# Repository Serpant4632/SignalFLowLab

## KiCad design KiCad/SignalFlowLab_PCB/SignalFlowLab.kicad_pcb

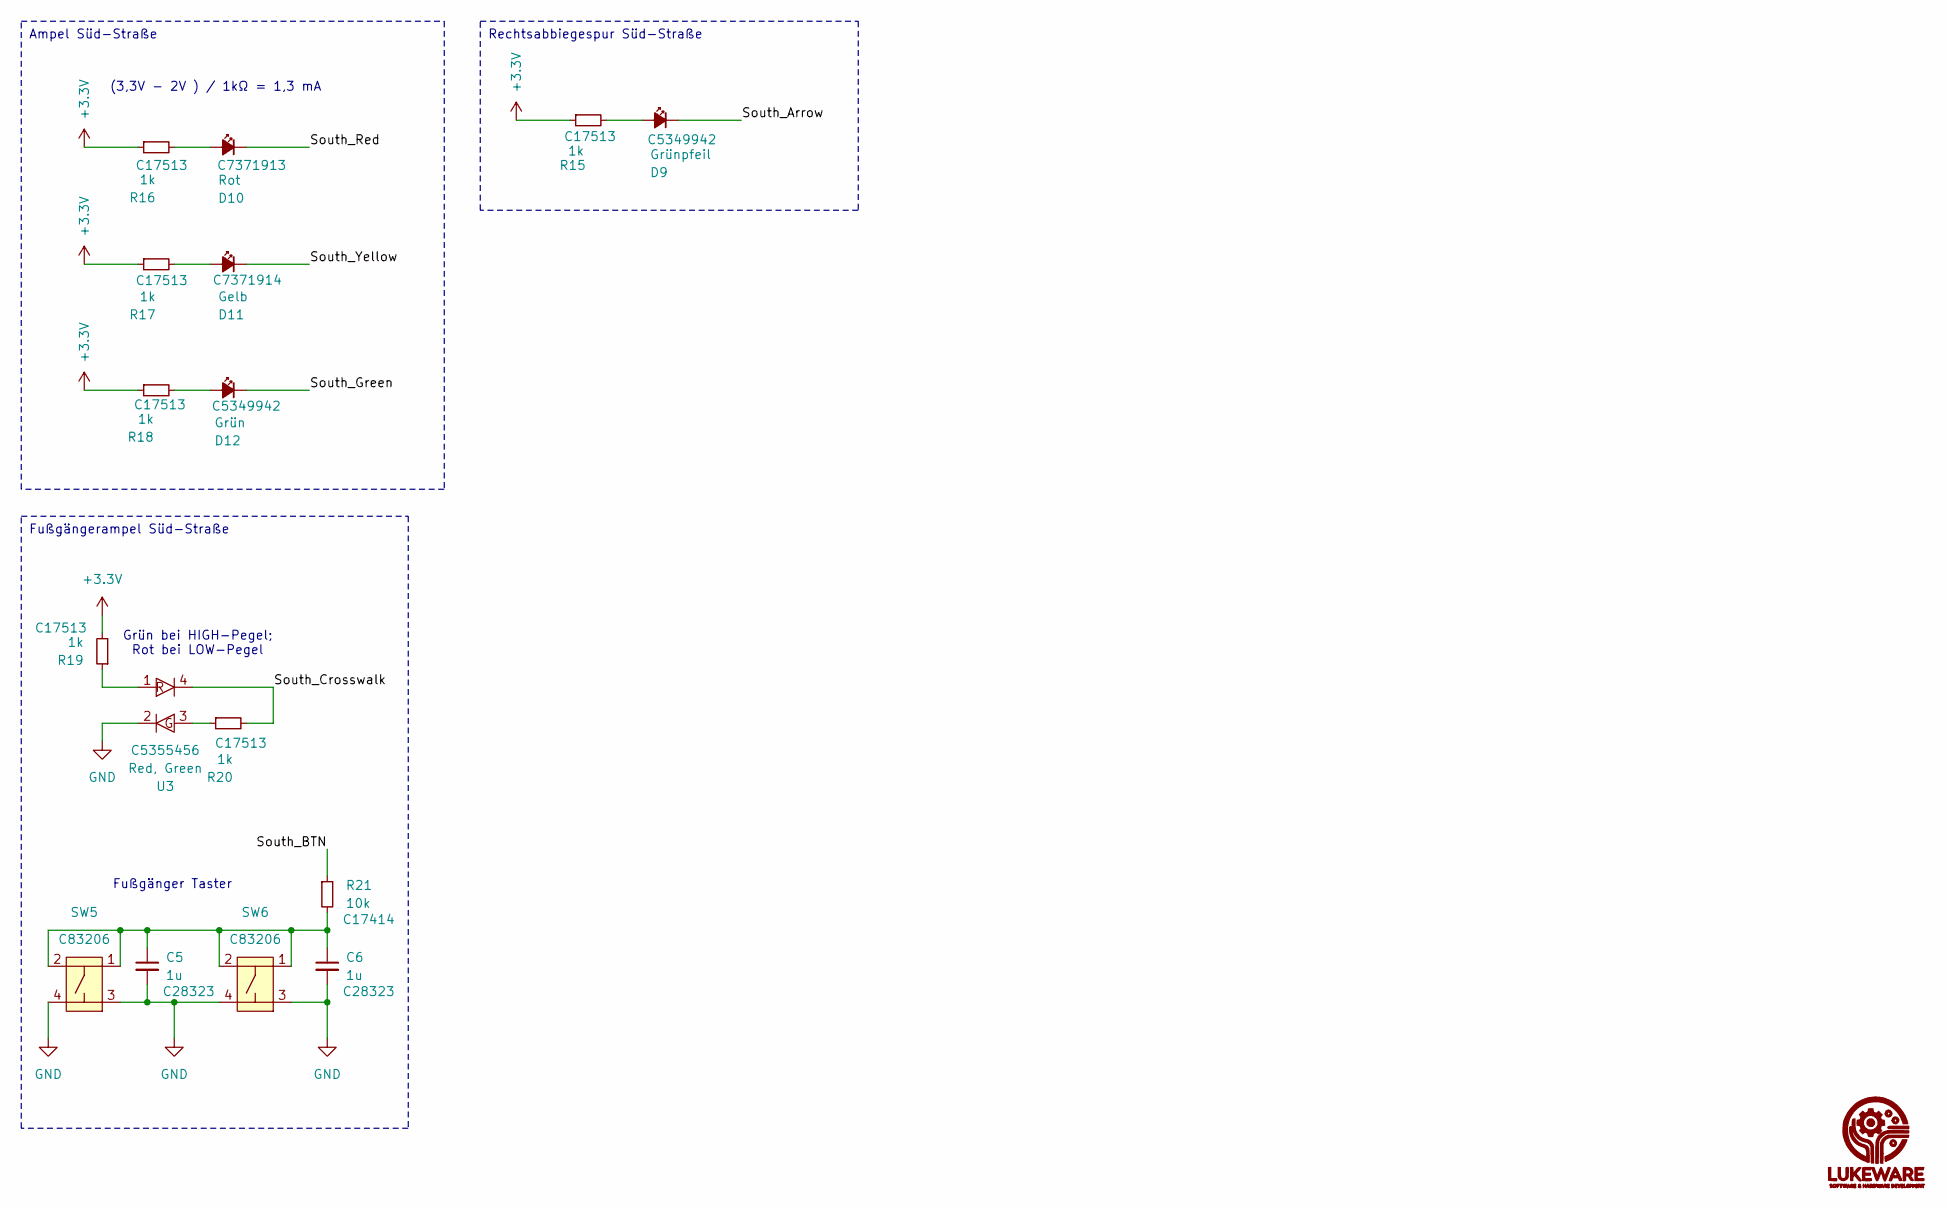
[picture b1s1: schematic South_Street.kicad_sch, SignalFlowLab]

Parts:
C5, C6: 1u; C_0805_2012Metric; LCSC C28323
D9: Grünpfeil; LED_0805_2012Metric; LCSC C5349942
D10: Rot; LED_0805_2012Metric; LCSC C7371913
D11: Gelb; LED_0805_2012Metric; LCSC C7371914
D12: Grün; LED_0805_2012Metric; LCSC C5349942
R15, R16, R17, R18, R19, R20: 1k; R_0805_2012Metric; LCSC C17513
R21: 10k; R_0805_2012Metric; LCSC C17414
SW5, SW6: K2-6639SP-C4SC-04; LCSC C83206
U3: Red, Green; A-SC6302R6AGHC-A03-2T; LCSC C5355456

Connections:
+3.3V: R15.1, R16.1, R17.1, R18.1, R19.2; also elsewhere on the board
/South_Street/South_Arrow: D9.1 (K)
/South_Street/South_BTN: R21.1
/South_Street/South_Crosswalk: R20.2, U3.4
/South_Street/South_Green: D12.1 (K)
/South_Street/South_Red: D10.1 (K)
/South_Street/South_Yellow: D11.1 (K)
GND: C5.2, C6.2, SW5.3, SW5.4, SW6.3, SW6.4, U3.2; also elsewhere on the board
unnamed: C5.1, C6.1, R21.2, SW5.1, SW5.2, SW6.1, SW6.2
unnamed: D9.2 (A), R15.2
unnamed: D10.2 (A), R16.2
unnamed: D11.2 (A), R17.2
unnamed: D12.2 (A), R18.2
unnamed: R19.1, U3.1
unnamed: R20.1, U3.3

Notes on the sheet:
Fußgängerampel Süd-Straße
Rechtsabbiegespur Süd-Straße
Ampel Süd-Straße
Grün bei HIGH-Pegel; Rot bei LOW-Pegel
Fußgänger Taster
(3,3V - 2V ) / 1kΩ = 1,3 mA

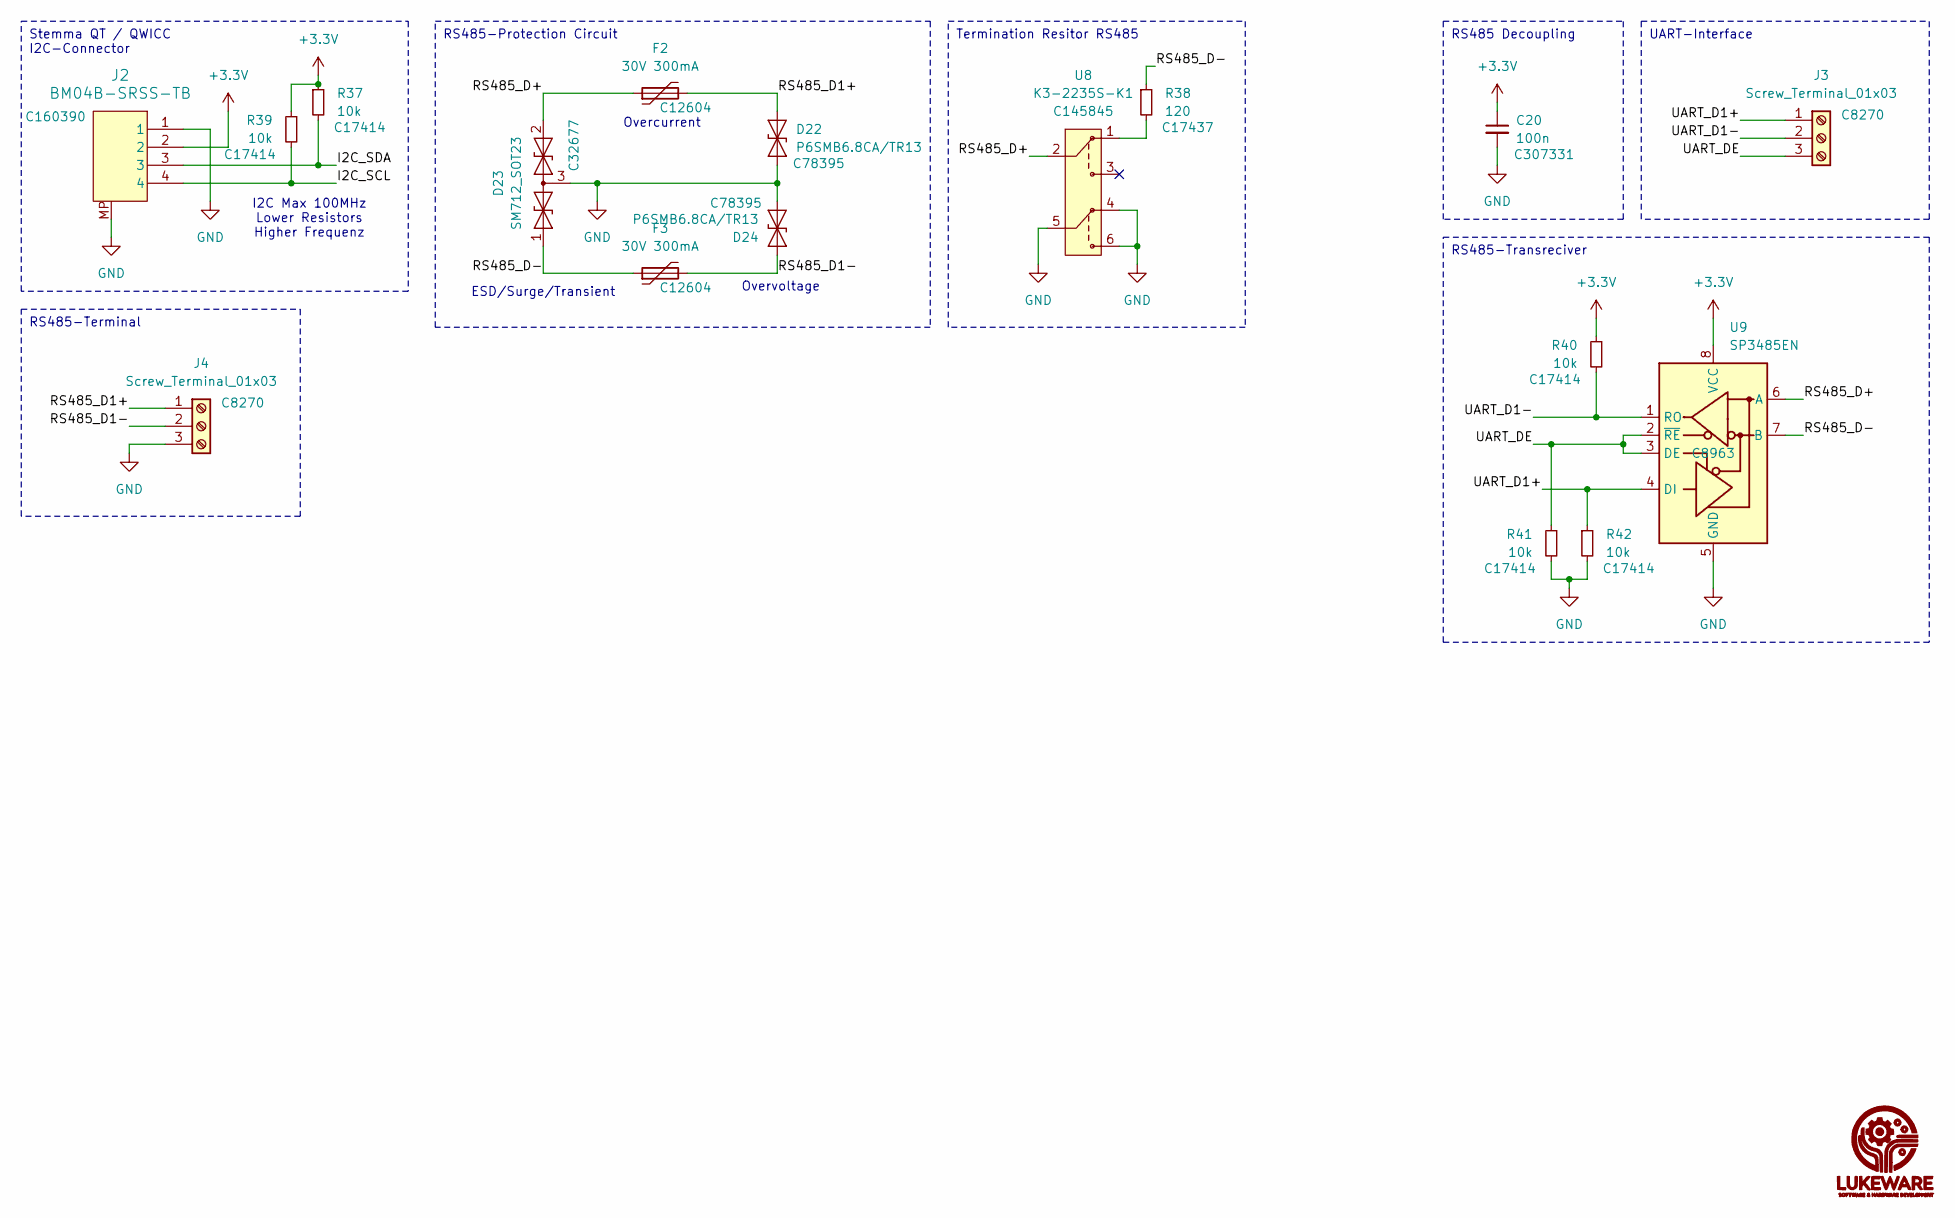
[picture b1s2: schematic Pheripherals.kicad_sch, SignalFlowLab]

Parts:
C20: 100n; C_0402_1005Metric; LCSC C307331
D22, D24: P6SMB6.8CA/TR13; D_SMB; LCSC C78395
D23: SM712_SOT23; SOT-23; LCSC C32677
F2, F3: 30V 300mA; Fuse_1812_4532Metric; LCSC C12604
J2: BM04B-SRSS-TB; CONN4_BM04B-SRSS_JST; LCSC C160390
J3, J4: Screw_Terminal_01x03; TerminalBlock_Phoenix_PT-1,5-3-5.0-H_1x03_P5.00mm_Horizontal; LCSC C8270
R37, R39, R40, R41, R42: 10k; R_0805_2012Metric; LCSC C17414
R38: 120; R_0805_2012Metric; LCSC C17437
U8: K3-2235S-K1; LCSC C145845
U9: SP3485EN; SOIC-8_3.9x4.9mm_P1.27mm; LCSC C8963

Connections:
+3.3V: C20.1, J2.2, R37.1, R39.1, R40.1, U9.8 (VCC); also elsewhere on the board
/Pheripherals/I2C_SCL: J2.4, R39.2
/Pheripherals/I2C_SDA: J2.3, R37.2
/Pheripherals/RS485_D1+: D22.2 (A2), F2.2, J4.1
/Pheripherals/RS485_D1-: D24.2 (A2), F3.2, J4.2
/Pheripherals/RS485_D+: D23.2 (A2), F2.1, U8.2, U9.6 (A)
/Pheripherals/RS485_D-: D23.1 (A1), F3.1, R38.1, U9.7 (B)
/Pheripherals/UART_D1+: J3.1, R42.1, U9.4 (DI)
/Pheripherals/UART_D1-: J3.2, R40.2, U9.1 (RO)
/Pheripherals/UART_DE: J3.3, R41.1, U9.2 (~RE), U9.3 (DE)
GND: C20.2, D22.1 (A1), D23.3 (common), D24.1 (A1), J2.1, J2.MP, J4.3, R41.2, R42.2, U8.4, U8.5, U8.6, U9.5 (GND); also elsewhere on the board
unnamed: R38.2, U8.1

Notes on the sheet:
Termination Resitor RS485
Stemma QT / QWICC I2C-Connector
RS485 Decoupling
RS485-Transreciver
RS485-Terminal
RS485-Protection Circuit
UART-Interface
ESD/Surge/Transient
Overvoltage
I2C Max 100MHz Lower Resistors Higher Frequenz
Overcurrent

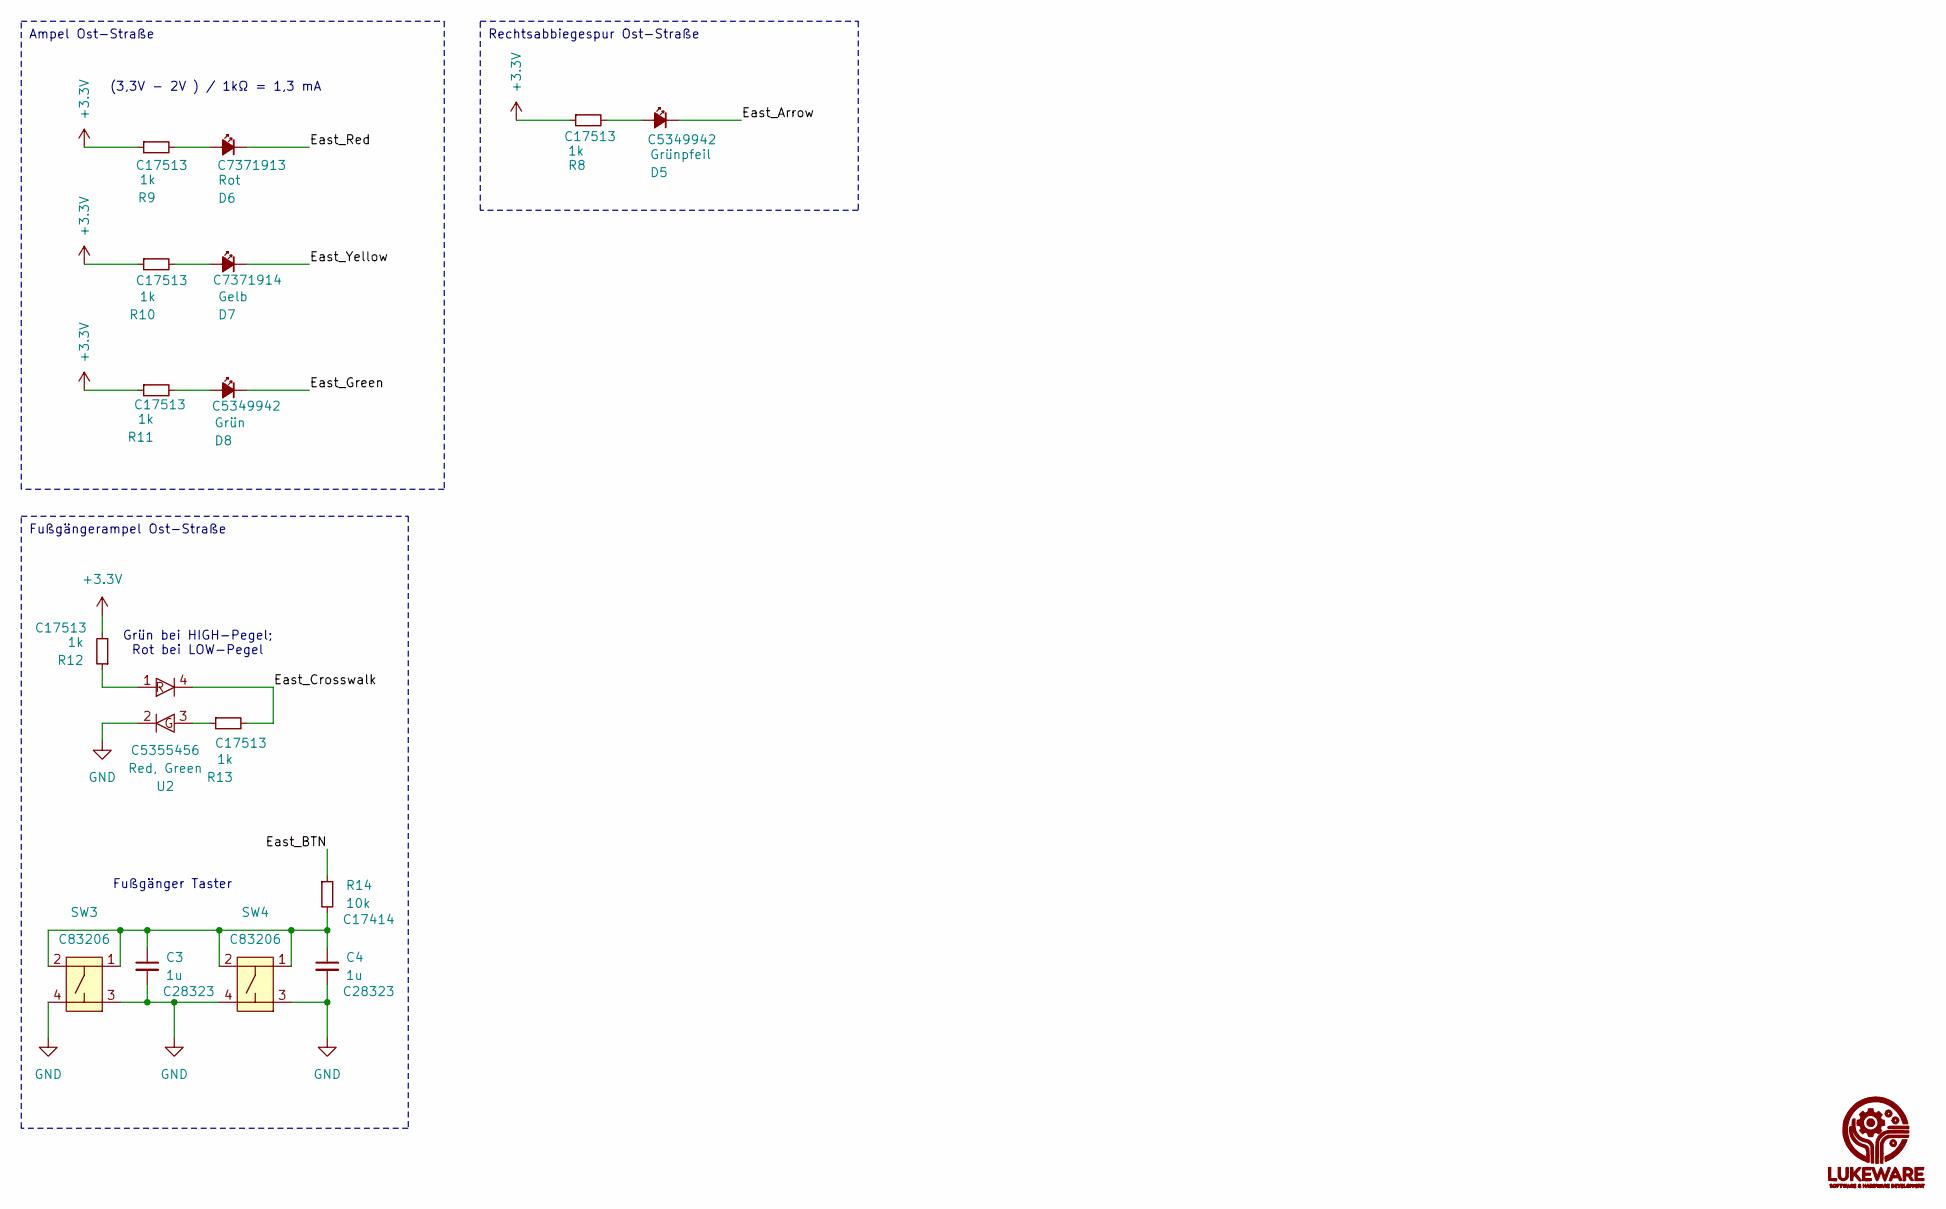
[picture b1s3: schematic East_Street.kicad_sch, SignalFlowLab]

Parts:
C3, C4: 1u; C_0805_2012Metric; LCSC C28323
D5: Grünpfeil; LED_0805_2012Metric; LCSC C5349942
D6: Rot; LED_0805_2012Metric; LCSC C7371913
D7: Gelb; LED_0805_2012Metric; LCSC C7371914
D8: Grün; LED_0805_2012Metric; LCSC C5349942
R8, R9, R10, R11, R12, R13: 1k; R_0805_2012Metric; LCSC C17513
R14: 10k; R_0805_2012Metric; LCSC C17414
SW3, SW4: K2-6639SP-C4SC-04; LCSC C83206
U2: Red, Green; A-SC6302R6AGHC-A03-2T; LCSC C5355456

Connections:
+3.3V: R8.1, R9.1, R10.1, R11.1, R12.2; also elsewhere on the board
/East_Street/East_Arrow: D5.1 (K)
/East_Street/East_BTN: R14.1
/East_Street/East_Crosswalk: R13.2, U2.4
/East_Street/East_Green: D8.1 (K)
/East_Street/East_Red: D6.1 (K)
/East_Street/East_Yellow: D7.1 (K)
GND: C3.2, C4.2, SW3.3, SW3.4, SW4.3, SW4.4, U2.2; also elsewhere on the board
unnamed: C3.1, C4.1, R14.2, SW3.1, SW3.2, SW4.1, SW4.2
unnamed: D5.2 (A), R8.2
unnamed: D6.2 (A), R9.2
unnamed: D7.2 (A), R10.2
unnamed: D8.2 (A), R11.2
unnamed: R12.1, U2.1
unnamed: R13.1, U2.3

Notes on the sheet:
Fußgängerampel Ost-Straße
Rechtsabbiegespur Ost-Straße
Ampel Ost-Straße
Grün bei HIGH-Pegel; Rot bei LOW-Pegel
Fußgänger Taster
(3,3V - 2V ) / 1kΩ = 1,3 mA

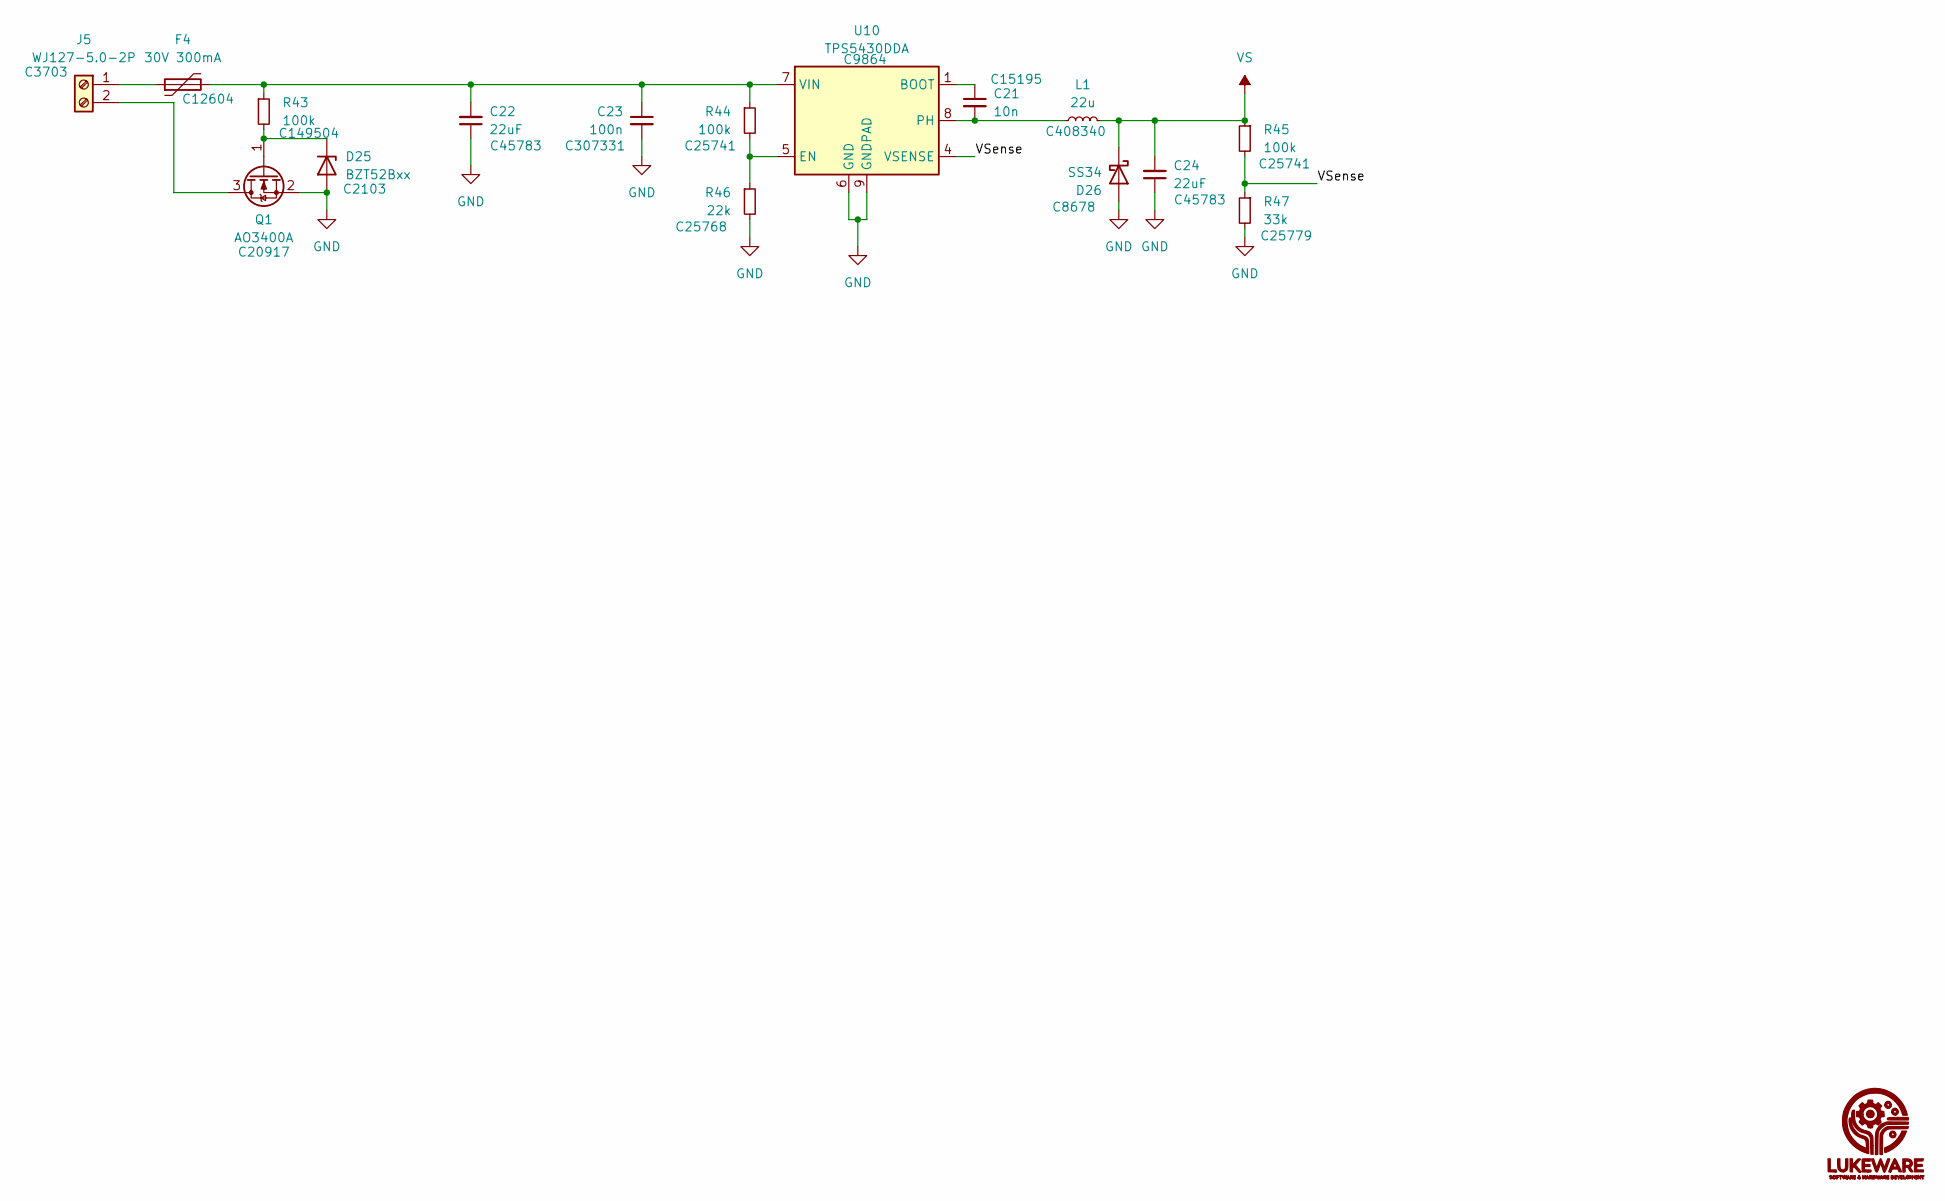
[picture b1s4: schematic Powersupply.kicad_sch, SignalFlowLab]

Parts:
C21: 10n; C_0402_1005Metric; LCSC C15195
C22, C24: 22uF; C_0805_2012Metric; LCSC C45783
C23: 100n; C_0402_1005Metric; LCSC C307331
D25: BZT52Bxx; D_SOD-123; LCSC C2103
D26: SS34; D_SMA; LCSC C8678
F4: 30V 300mA; Fuse_1812_4532Metric; LCSC C12604
J5: WJ127-5.0-2P; TerminalBlock_Phoenix_PT-1,5-2-5.0-H_1x02_P5.00mm_Horizontal; LCSC C3703
L1: 22u; L_Sunlord_MWSA0402S; LCSC C408340
Q1: AO3400A; SOT-23; LCSC C20917
R43: 100k; C_0805_2012Metric; LCSC C149504
R44, R45: 100k; R_0402_1005Metric; LCSC C25741
R46: 22k; R_0402_1005Metric; LCSC C25768
R47: 33k; R_0402_1005Metric; LCSC C25779
U10: TPS5430DDA; TI_SO-PowerPAD-8_ThermalVias; LCSC C9864

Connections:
/Powersupply/VSense: R45.2, R47.1, U10.4 (VSENSE)
GND: C22.1, C23.2, C24.1, D25.2 (A), D26.2 (A), Q1.2 (S), R46.2, R47.2, U10.6 (GND), U10.9 (GNDPAD); also elsewhere on the board
unnamed: D25.1 (K), Q1.1 (G), R43.2
unnamed: F4.1, J5.1
unnamed: J5.2, Q1.3 (D)
unnamed: C21.1, U10.1 (BOOT)
unnamed: R44.2, R46.1, U10.5 (EN)
unnamed: C21.2, L1.2, U10.8 (PH)
unnamed: C22.2, C23.1, F4.2, R43.1, R44.1, U10.7 (VIN)
VS: C24.2, D26.1 (K), L1.1, R45.1; also elsewhere on the board

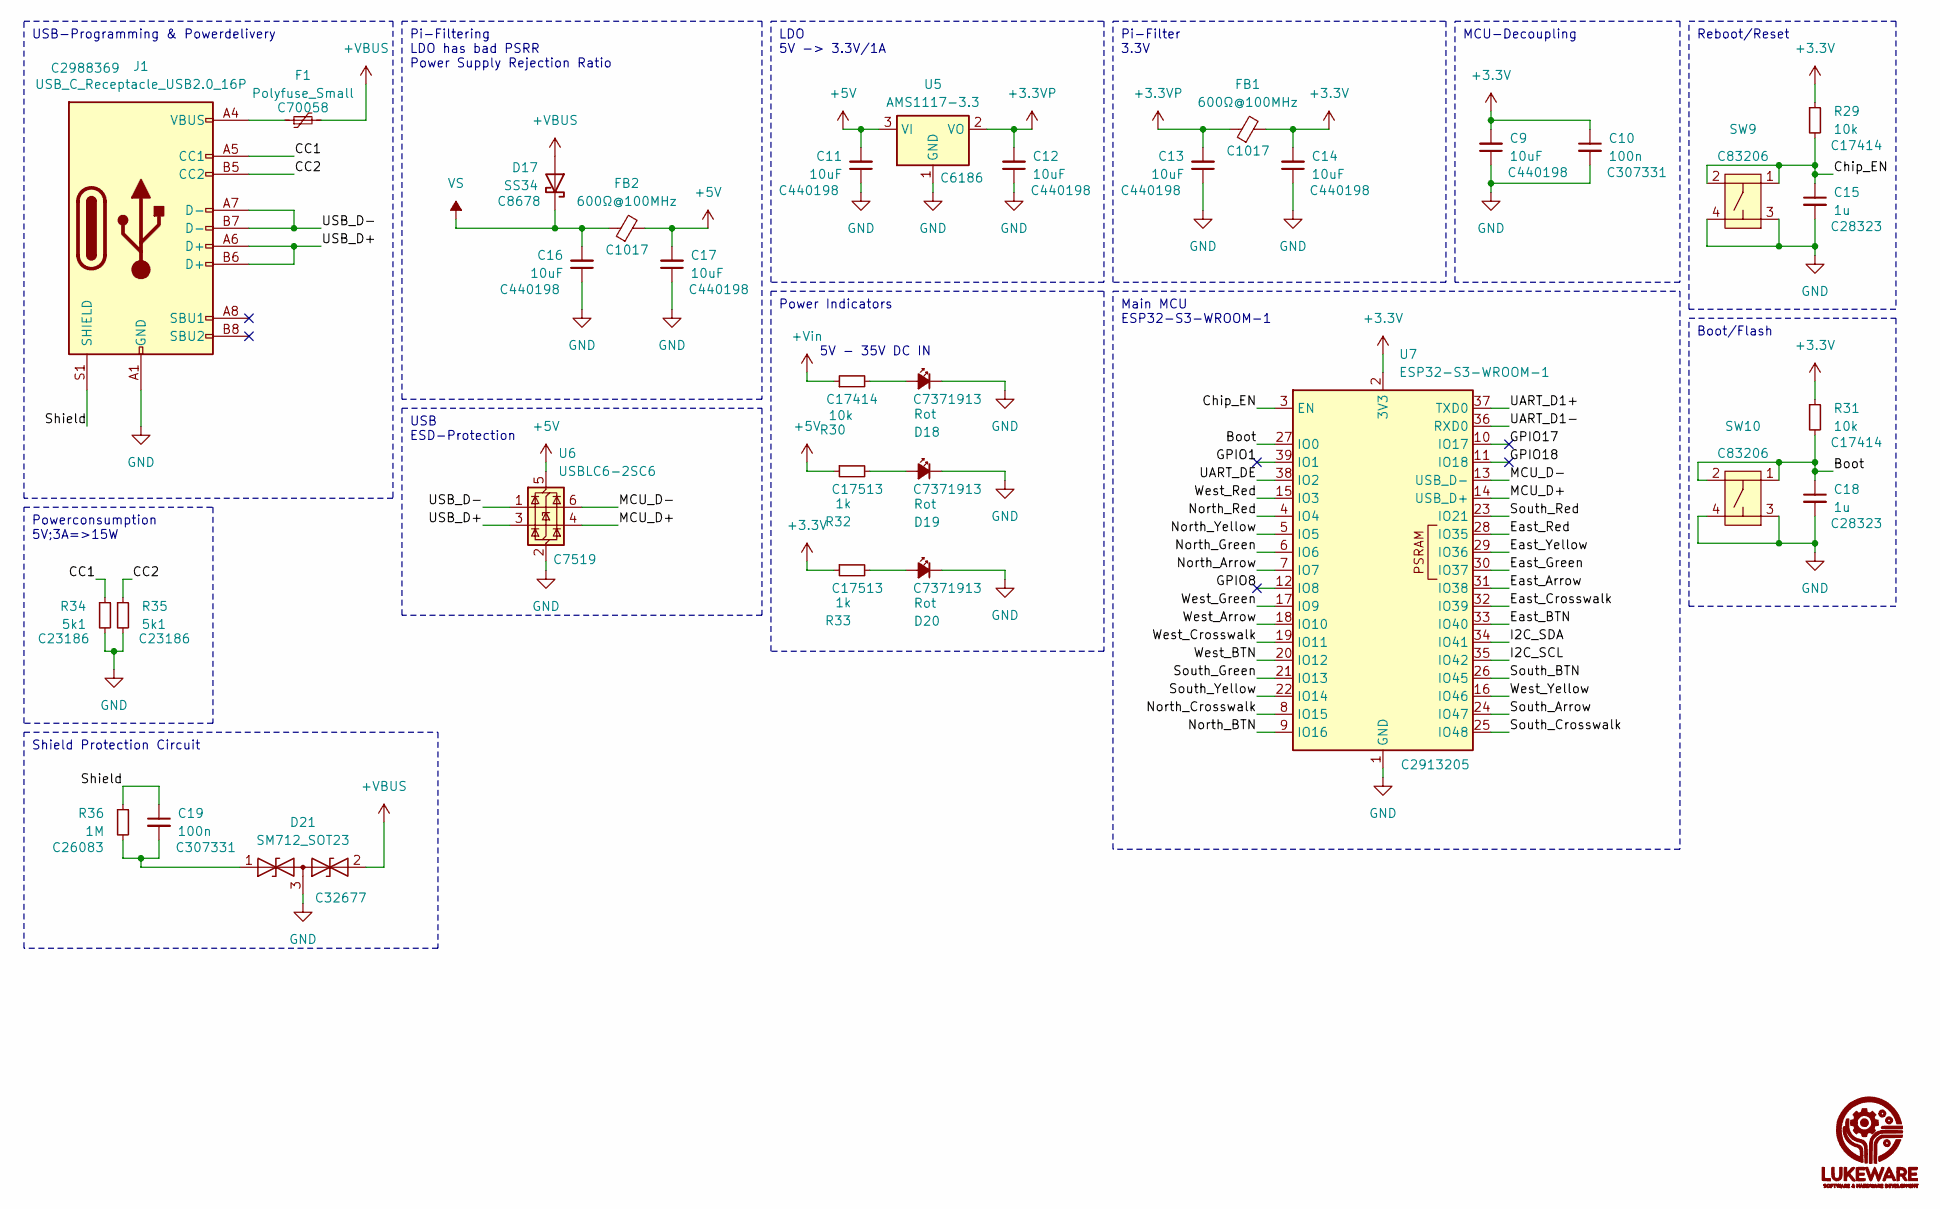
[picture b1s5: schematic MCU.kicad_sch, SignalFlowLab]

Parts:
C9, C11, C12, C13, C14, C16, C17: 10uF; C_0805_2012Metric; LCSC C440198
C10, C19: 100n; C_0402_1005Metric; LCSC C307331
C15, C18: 1u; C_0805_2012Metric; LCSC C28323
D17: SS34; D_SMA; LCSC C8678
D18, D19, D20: Rot; LED_0805_2012Metric; LCSC C7371913
D21: SM712_SOT23; SOT-23; LCSC C32677
F1: Polyfuse_Small; Fuse_0805_2012Metric; LCSC C70058
FB1, FB2: 600Ω@100MHz; L_0805_2012Metric; LCSC C1017
J1: USB_C_Receptacle_USB2.0_16P; USB_C_Receptacle_G-Switch_GT-USB-7010ASV; LCSC C2988369
R29, R30, R31: 10k; R_0805_2012Metric; LCSC C17414
R32, R33: 1k; R_0805_2012Metric; LCSC C17513
R34, R35: 5k1; R_0603_1608Metric; LCSC C23186
R36: 1M; R_0402_1005Metric; LCSC C26083
SW9, SW10: K2-6639SP-C4SC-04; LCSC C83206
U5: AMS1117-3.3; SOT-223-3_TabPin2; LCSC C6186
U6: USBLC6-2SC6; SOT-23-6; LCSC C7519
U7: ESP32-S3-WROOM-1; LCSC C2913205

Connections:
+3.3V: C9.2, C10.1, C14.2, FB1.2, R29.1, R31.1, R33.1, U7.2 (3V3); also elsewhere on the board
+3.3VP: C12.2, C13.2, FB1.1, U5.2 (VO)
+5V: C11.2, C17.2, FB2.2, R32.1, U5.3 (VI), U6.5 (VBUS)
+VBUS: D17.2 (A), D21.2 (A2), F1.2
+Vin: R30.1
/MCU/Boot: C18.1, R31.2, SW10.1, SW10.2, U7.27 (IO0)
/MCU/CC1: J1.A5 (CC1), R34.1
/MCU/CC2: J1.B5 (CC2), R35.1
/MCU/Chip_EN: C15.1, R29.2, SW9.1, SW9.2, U7.3 (EN)
/MCU/East_Arrow: U7.31 (IO38)
/MCU/East_BTN: U7.33 (IO40)
/MCU/East_Crosswalk: U7.32 (IO39)
/MCU/East_Green: U7.30 (IO37)
/MCU/East_Red: U7.28 (IO35)
/MCU/East_Yellow: U7.29 (IO36)
/MCU/GPIO1: U7.39 (IO1)
/MCU/GPIO8: U7.12 (IO8)
/MCU/GPIO17: U7.10 (IO17)
/MCU/GPIO18: U7.11 (IO18)
/MCU/I2C_SCL: U7.35 (IO42)
/MCU/I2C_SDA: U7.34 (IO41)
/MCU/MCU_D+: U6.4 (I/O2), U7.14 (USB_D+)
/MCU/MCU_D-: U6.6 (I/O1), U7.13 (USB_D-)
/MCU/North_Arrow: U7.7 (IO7)
/MCU/North_BTN: U7.9 (IO16)
/MCU/North_Crosswalk: U7.8 (IO15)
/MCU/North_Green: U7.6 (IO6)
/MCU/North_Red: U7.4 (IO4)
/MCU/North_Yellow: U7.5 (IO5)
/MCU/Shield: C19.1, J1.S1 (SHIELD), R36.1
/MCU/South_Arrow: U7.24 (IO47)
/MCU/South_BTN: U7.26 (IO45)
/MCU/South_Crosswalk: U7.25 (IO48)
/MCU/South_Green: U7.21 (IO13)
/MCU/South_Red: U7.23 (IO21)
/MCU/South_Yellow: U7.22 (IO14)
/MCU/UART_D1+: U7.37 (TXD0)
/MCU/UART_D1-: U7.36 (RXD0)
/MCU/UART_DE: U7.38 (IO2)
/MCU/USB_D+: J1.A6 (D+), J1.B6 (D+), U6.3 (I/O2)
/MCU/USB_D-: J1.A7 (D-), J1.B7 (D-), U6.1 (I/O1)
/MCU/West_Arrow: U7.18 (IO10)
/MCU/West_BTN: U7.20 (IO12)
/MCU/West_Crosswalk: U7.19 (IO11)
/MCU/West_Green: U7.17 (IO9)
/MCU/West_Red: U7.15 (IO3)
/MCU/West_Yellow: U7.16 (IO46)
GND: C9.1, C10.2, C11.1, C12.1, C13.1, C14.1, C15.2, C16.1, C17.1, C18.2, D18.1 (K), D19.1 (K), D20.1 (K), D21.3 (common), J1.A1 (GND), J1.A12 (GND), J1.B1 (GND), J1.B12 (GND), R34.2, R35.2, SW9.3, SW9.4, SW10.3, SW10.4, U5.1 (GND), U6.2 (GND), U7.1 (GND), U7.40 (GND), U7.41 (GND); also elsewhere on the board
unnamed: D18.2 (A), R30.2
unnamed: D19.2 (A), R32.2
unnamed: D20.2 (A), R33.2
unnamed: C19.2, D21.1 (A1), R36.2
unnamed: F1.1, J1.A4 (VBUS), J1.A9 (VBUS), J1.B4 (VBUS), J1.B9 (VBUS)
VS: C16.2, D17.1 (K), FB2.1; also elsewhere on the board

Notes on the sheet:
Pi-Filter 3.3V
Reboot/Reset
Power Indicators
USB-Programming & Powerdelivery
Shield Protection Circuit
MCU-Decoupling
USB ESD-Protection
LDO 5V -> 3.3V/1A
Pi-Filtering LDO has bad PSRR Power Supply Rejection Ratio
Main MCU ESP32-S3-WROOM-1
Powerconsumption 5V;3A=>15W
Boot/Flash
5V - 35V DC IN

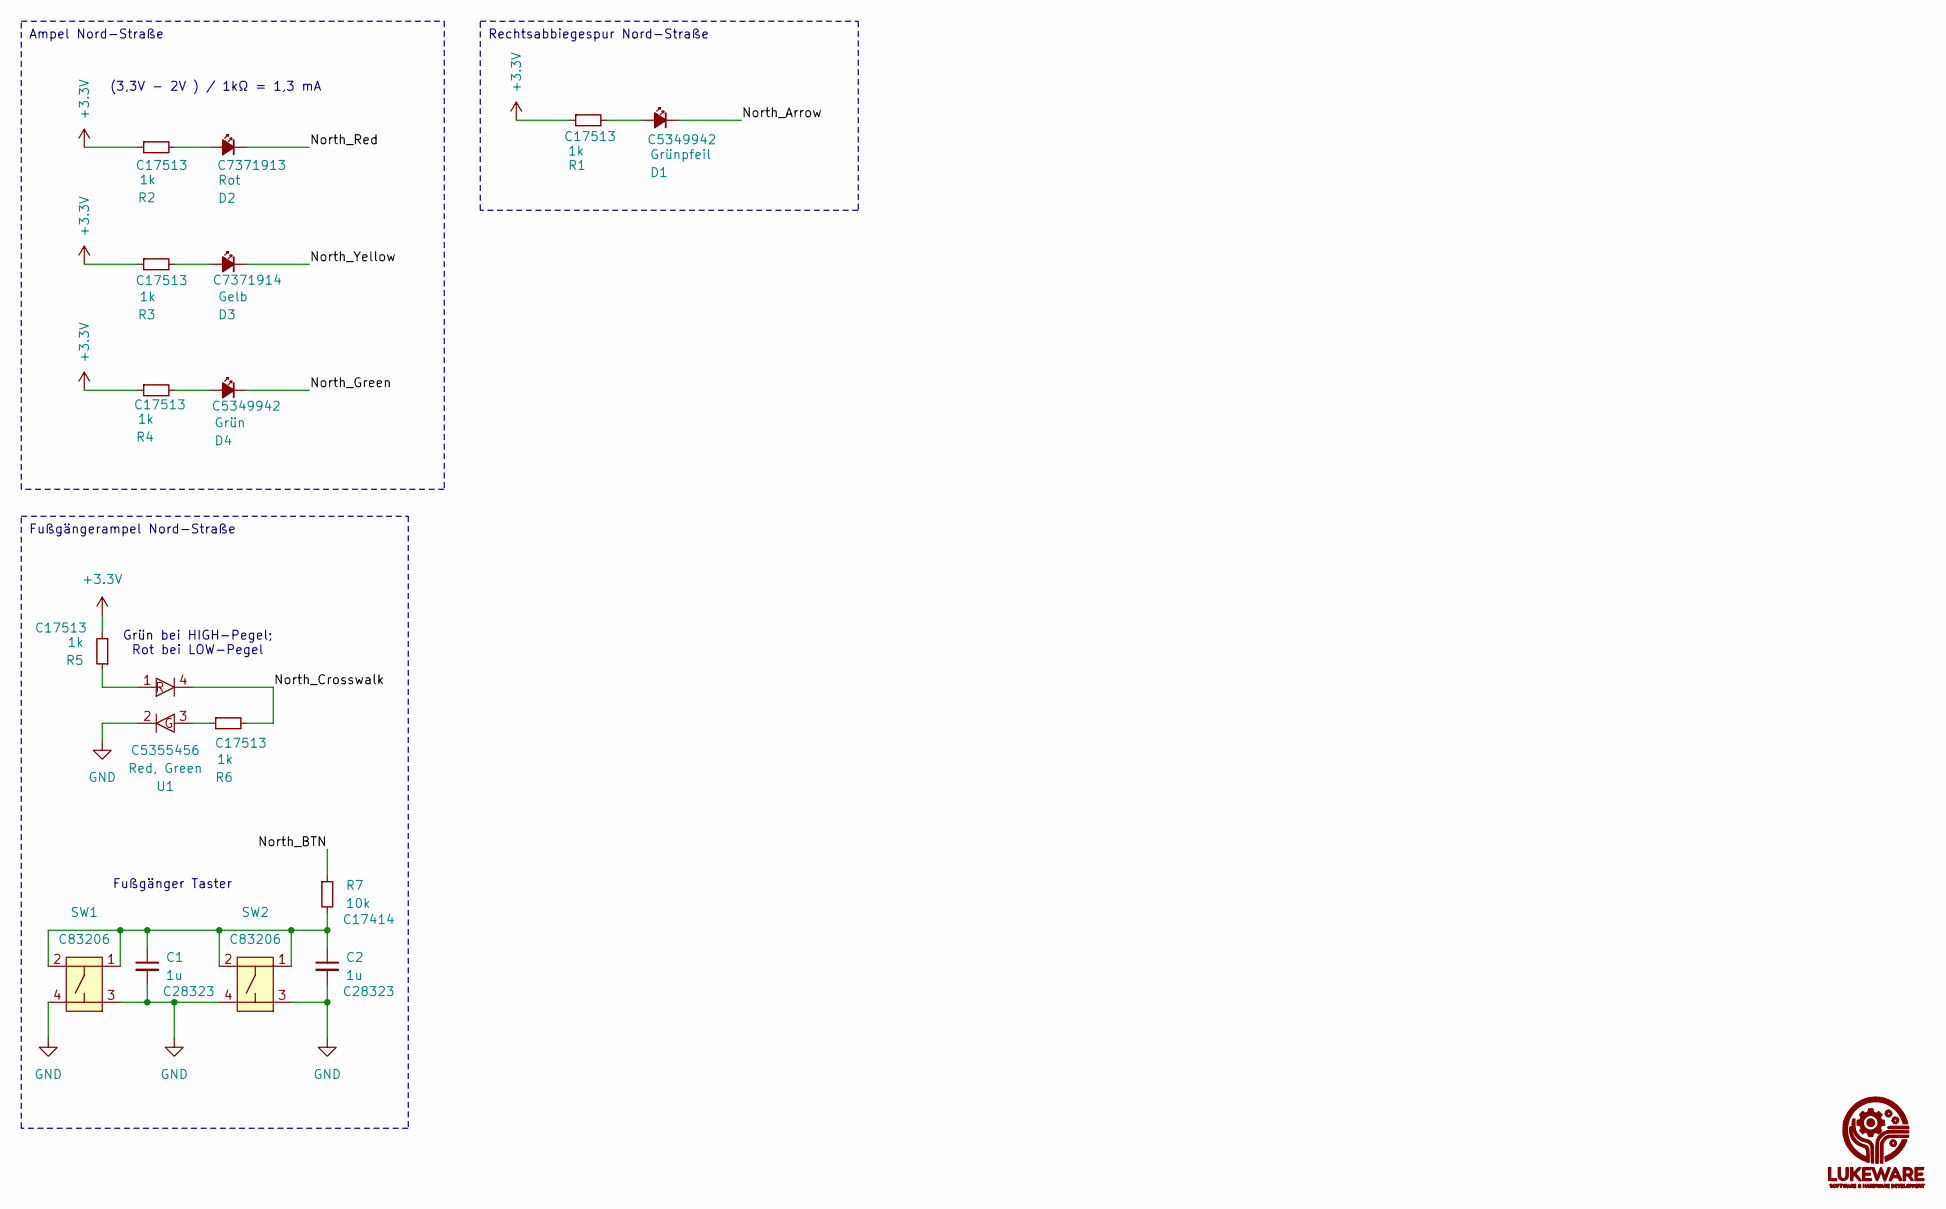
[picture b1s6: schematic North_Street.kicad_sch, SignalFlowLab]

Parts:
C1, C2: 1u; C_0805_2012Metric; LCSC C28323
D1: Grünpfeil; LED_0805_2012Metric; LCSC C5349942
D2: Rot; LED_0805_2012Metric; LCSC C7371913
D3: Gelb; LED_0805_2012Metric; LCSC C7371914
D4: Grün; LED_0805_2012Metric; LCSC C5349942
R1, R2, R3, R4, R5, R6: 1k; R_0805_2012Metric; LCSC C17513
R7: 10k; R_0805_2012Metric; LCSC C17414
SW1, SW2: K2-6639SP-C4SC-04; LCSC C83206
U1: Red, Green; A-SC6302R6AGHC-A03-2T; LCSC C5355456

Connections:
+3.3V: R1.1, R2.1, R3.1, R4.1, R5.2; also elsewhere on the board
/North_Street/North_Arrow: D1.1 (K)
/North_Street/North_BTN: R7.1
/North_Street/North_Crosswalk: R6.2, U1.4
/North_Street/North_Green: D4.1 (K)
/North_Street/North_Red: D2.1 (K)
/North_Street/North_Yellow: D3.1 (K)
GND: C1.2, C2.2, SW1.3, SW1.4, SW2.3, SW2.4, U1.2; also elsewhere on the board
unnamed: C1.1, C2.1, R7.2, SW1.1, SW1.2, SW2.1, SW2.2
unnamed: D1.2 (A), R1.2
unnamed: D2.2 (A), R2.2
unnamed: D3.2 (A), R3.2
unnamed: D4.2 (A), R4.2
unnamed: R5.1, U1.1
unnamed: R6.1, U1.3

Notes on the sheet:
Fußgängerampel Nord-Straße
Rechtsabbiegespur Nord-Straße
Ampel Nord-Straße
Grün bei HIGH-Pegel; Rot bei LOW-Pegel
Fußgänger Taster
(3,3V - 2V ) / 1kΩ = 1,3 mA

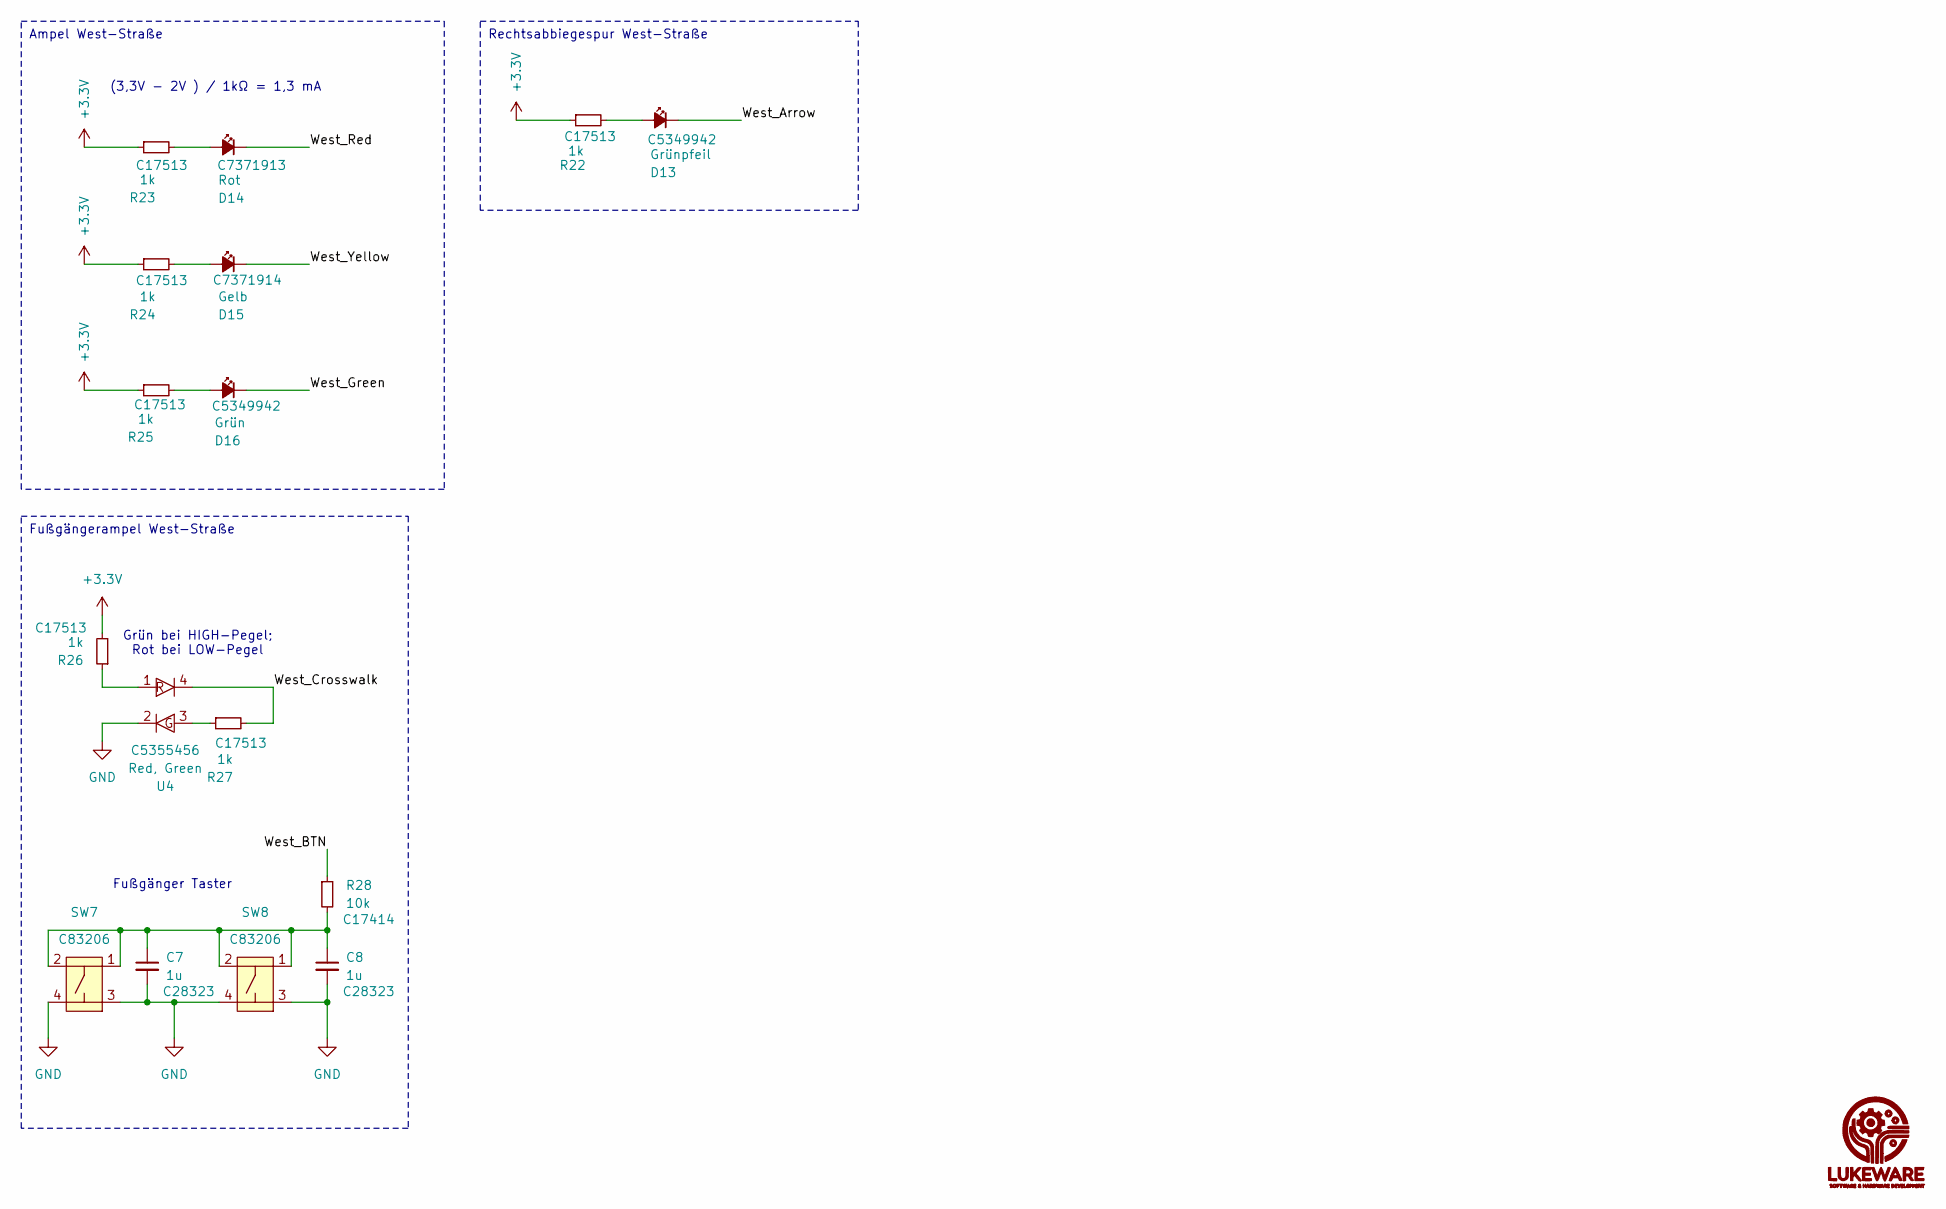
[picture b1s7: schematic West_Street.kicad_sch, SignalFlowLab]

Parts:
C7, C8: 1u; C_0805_2012Metric; LCSC C28323
D13: Grünpfeil; LED_0805_2012Metric; LCSC C5349942
D14: Rot; LED_0805_2012Metric; LCSC C7371913
D15: Gelb; LED_0805_2012Metric; LCSC C7371914
D16: Grün; LED_0805_2012Metric; LCSC C5349942
R22, R23, R24, R25, R26, R27: 1k; R_0805_2012Metric; LCSC C17513
R28: 10k; R_0805_2012Metric; LCSC C17414
SW7, SW8: K2-6639SP-C4SC-04; LCSC C83206
U4: Red, Green; A-SC6302R6AGHC-A03-2T; LCSC C5355456

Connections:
+3.3V: R22.1, R23.1, R24.1, R25.1, R26.2; also elsewhere on the board
/West_Street/West_Arrow: D13.1 (K)
/West_Street/West_BTN: R28.1
/West_Street/West_Crosswalk: R27.2, U4.4
/West_Street/West_Green: D16.1 (K)
/West_Street/West_Red: D14.1 (K)
/West_Street/West_Yellow: D15.1 (K)
GND: C7.2, C8.2, SW7.3, SW7.4, SW8.3, SW8.4, U4.2; also elsewhere on the board
unnamed: C7.1, C8.1, R28.2, SW7.1, SW7.2, SW8.1, SW8.2
unnamed: D13.2 (A), R22.2
unnamed: D14.2 (A), R23.2
unnamed: D15.2 (A), R24.2
unnamed: D16.2 (A), R25.2
unnamed: R26.1, U4.1
unnamed: R27.1, U4.3

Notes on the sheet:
Fußgängerampel West-Straße
Rechtsabbiegespur West-Straße
Ampel West-Straße
Grün bei HIGH-Pegel; Rot bei LOW-Pegel
Fußgänger Taster
(3,3V - 2V ) / 1kΩ = 1,3 mA

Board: 2 copper layers, 130 parts (0 on the bottom side), 70 nets, no tracks yet.
